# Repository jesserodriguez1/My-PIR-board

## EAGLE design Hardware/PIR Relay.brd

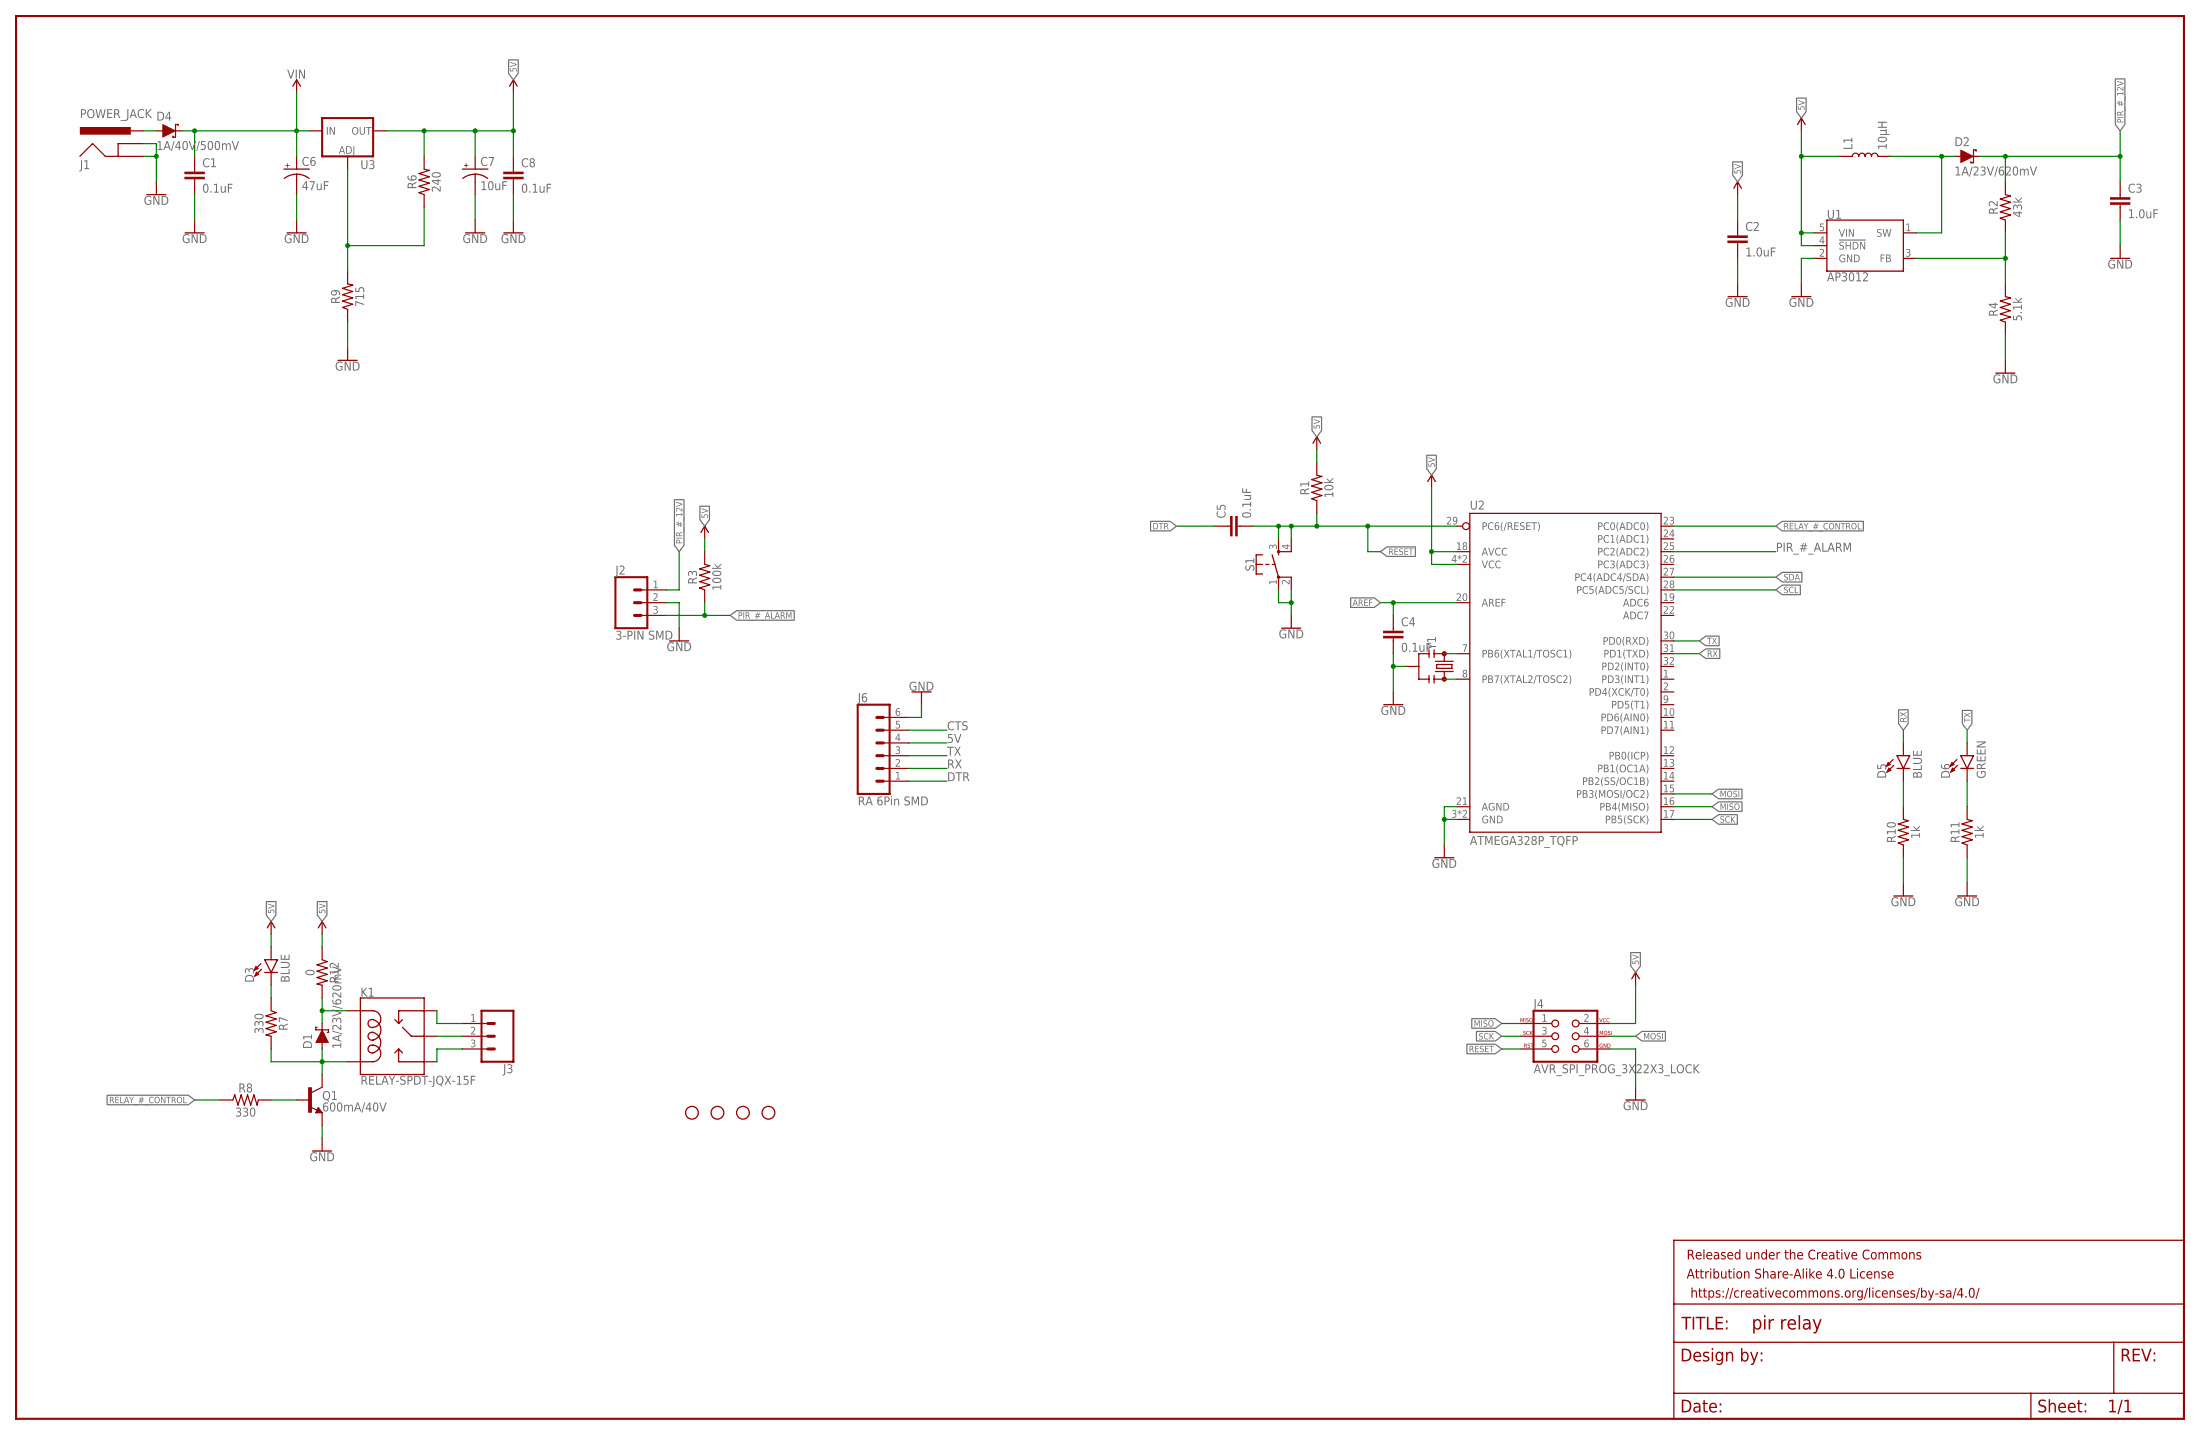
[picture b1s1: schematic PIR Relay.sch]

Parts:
C1, C4, C5, C8: 0.1uF; 0603
C2, C3: 1.0uF; 0603
C6: 47uF; PANASONIC_D
C7: 10uF; EIA3216
D1, D2: 1A/23V/620mV; SOD-323
D3, D5: BLUE; LED-0603
D4: 1A/40V/500mV; SMA-DIODE
D6: GREEN; LED-0603
FRAME1: FRAME-LEDGER; CREATIVE_COMMONS
H1, H2, H3, H4: STAND-OFF
J1: POWER_JACK; POWER_JACK_PTH
J2: 3-PIN SMD; JST-3-SMD
J3: CONN_03SCREW_LOCK; SCREWTERMINAL-3.5MM-3_LOCK.007S
J4: AVR_SPI_PROG_3X22X3_LOCK; 2X3_LOCK
J6: RA 6Pin SMD; 1X06-SMD_RA_MALE
K1: RELAY-SPDT-JQX-15F; RELAY-T90
L1: 10μH; 0805
Q1: 600mA/40V; SOT23-3
R1: 10k; 0603
R2: 43k; 0603
R3: 100k; 0603
R4: 5.1k; 0603
R6: 240; 0603
R7, R8: 330; 0603
R9: 715; 0603
R10, R11: 1k; 0603
R12: 0; 0603
S1: MOMENTARY-SWITCH-SPST-2-SMD-5.2MM-TALL; TACTILE_SWITCH_SMD_5.2MM
U1: AP3012; SOT23-5
U2: ATMEGA328P_TQFP; TQFP32-08
U3: V_REG_LM1117SOT223; SOT223
Y1: RESONATORSMD-3.2X1.3; RESONATOR-SMD-3.2X1.3

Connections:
5V: C2.1, C7.+, C8.1, D3.A, J4.2, J6.4, L1.1, R1.2, R3.2, R6.2, R12.1, U1.4 (!SHDN!), U1.5 (VIN), U2.4 (VCC), U2.6 (VCC), U2.18 (AVCC), U3.2 (OUT), U3.4 (OUT)
AREF: C4.1, U2.20 (AREF)
COM: J3.2, K1.MAIN
CTS: J6.5
DTR: C5.1, J6.1
FTDI-RX: D5.A, J6.2, U2.31 (PD1(TXD))
FTDI-TX: D6.A, J6.3, U2.30 (PD0(RXD))
GND: C1.2, C2.2, C3.2, C4.2, C6.-, C7.-, C8.2, J1.GND, J1.GNDBREAK, J2.2, J4.6, J6.6, Q1.2 (E), R4.1, R9.1, R10.1, R11.1, S1.1, S1.2, U1.2 (GND), U2.3 (GND), U2.5 (GND), U2.21 (AGND), Y1.2
MISO: J4.1, U2.16 (PB4(MISO))
MOSI: J4.4, U2.15 (PB3(MOSI/OC2))
unnamed: D2.A, L1.2, U1.1 (SW)
unnamed: D5.C, R10.2
unnamed: Q1.1 (B), R8.2
unnamed: D1.A, K1.COIL2, Q1.3 (C), R7.2
unnamed: D1.C, K1.COIL1, R12.2
unnamed: D3.C, R7.1
unnamed: U2.7 (PB6(XTAL1/TOSC1)), Y1.1
unnamed: U2.8 (PB7(XTAL2/TOSC2)), Y1.3
unnamed: D4.A, J1.PWR
unnamed: R6.1, R9.2, U3.1 (ADJ)
unnamed: D6.C, R11.2
unnamed: R2.1, R4.2, U1.3 (FB)
NC: J3.1, K1.NC
NO: J3.3, K1.NO
PIR_#_12V: C3.1, D2.C, J2.1 (3), R2.2
PIR_#_ALARM: J2.3 (1), R3.1, U2.25 (PC2(ADC2))
RELAY_#_CONTROL: R8.1, U2.23 (PC0(ADC0))
RESET: C5.2, J4.5, R1.1, S1.3, S1.4, U2.29 (PC6(/RESET))
SCK: J4.3, U2.17 (PB5(SCK))
SCL: U2.28 (PC5(ADC5/SCL))
SDA: U2.27 (PC4(ADC4/SDA))
VIN: C1.1, C6.+, D4.C, U3.3 (IN)

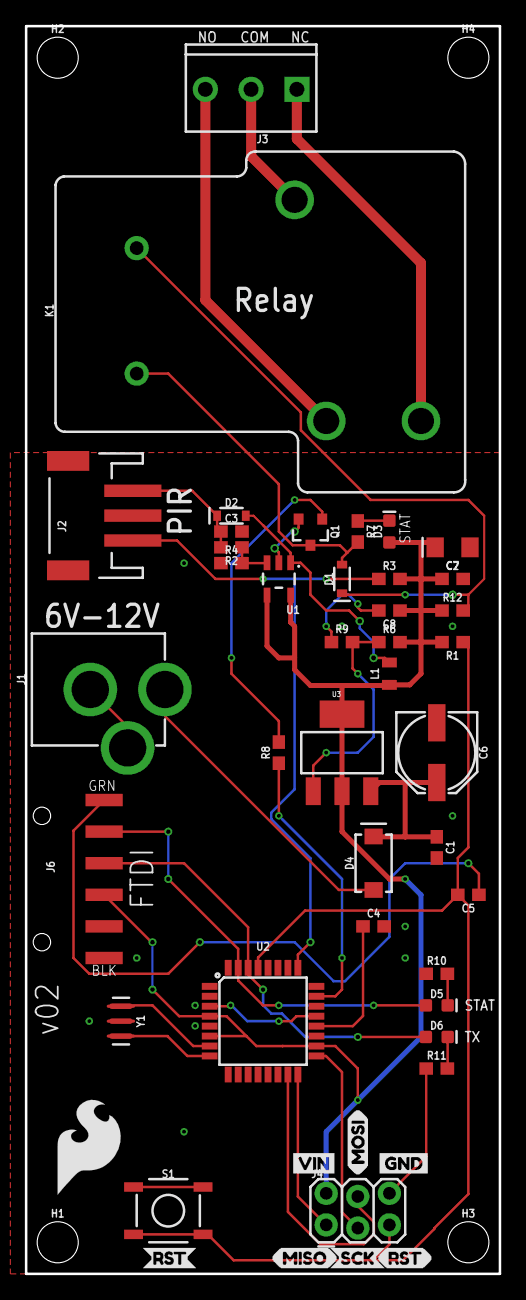
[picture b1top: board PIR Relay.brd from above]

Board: 2 copper layers, 38.1 x 100.3 mm, 51 parts (0 on the bottom side), 29 nets.

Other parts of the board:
U$1: MISO_I
U$2: MOSI_I
U$3: RST_I
U$4: SCK_O
U$5: GND_P
U$6: VIN_P
U$7: RST_O
U$9: SFE_LOGO_FLAME_.3

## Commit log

2020-11-25 add .brd and .sch files
2020-11-25 updated PIR Rlay Board
2020-11-25 removing old files
2020-11-25 update brd file
2020-12-10 PIR gerber generation
2021-02-15 updated code
2021-02-16 Rerouted. Fixed header problem
2021-02-16 swapped 47k for 0hm
2021-02-18 PIR Relay total revision

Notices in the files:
parts and their libraries:
SparkFun-Capacitors: Licensing: Creative Commons ShareAlike 4.0 International - https://creativecommons.org/licenses/by-sa/4.0
SparkFun-Aesthetics: Released under the Creative Commons Attribution Share-Alike 4.0 License
SparkFun-Aesthetics: https://creativecommons.org/licenses/by-sa/4.0
